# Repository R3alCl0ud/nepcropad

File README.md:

# nepcropad
Me macro pad kb files

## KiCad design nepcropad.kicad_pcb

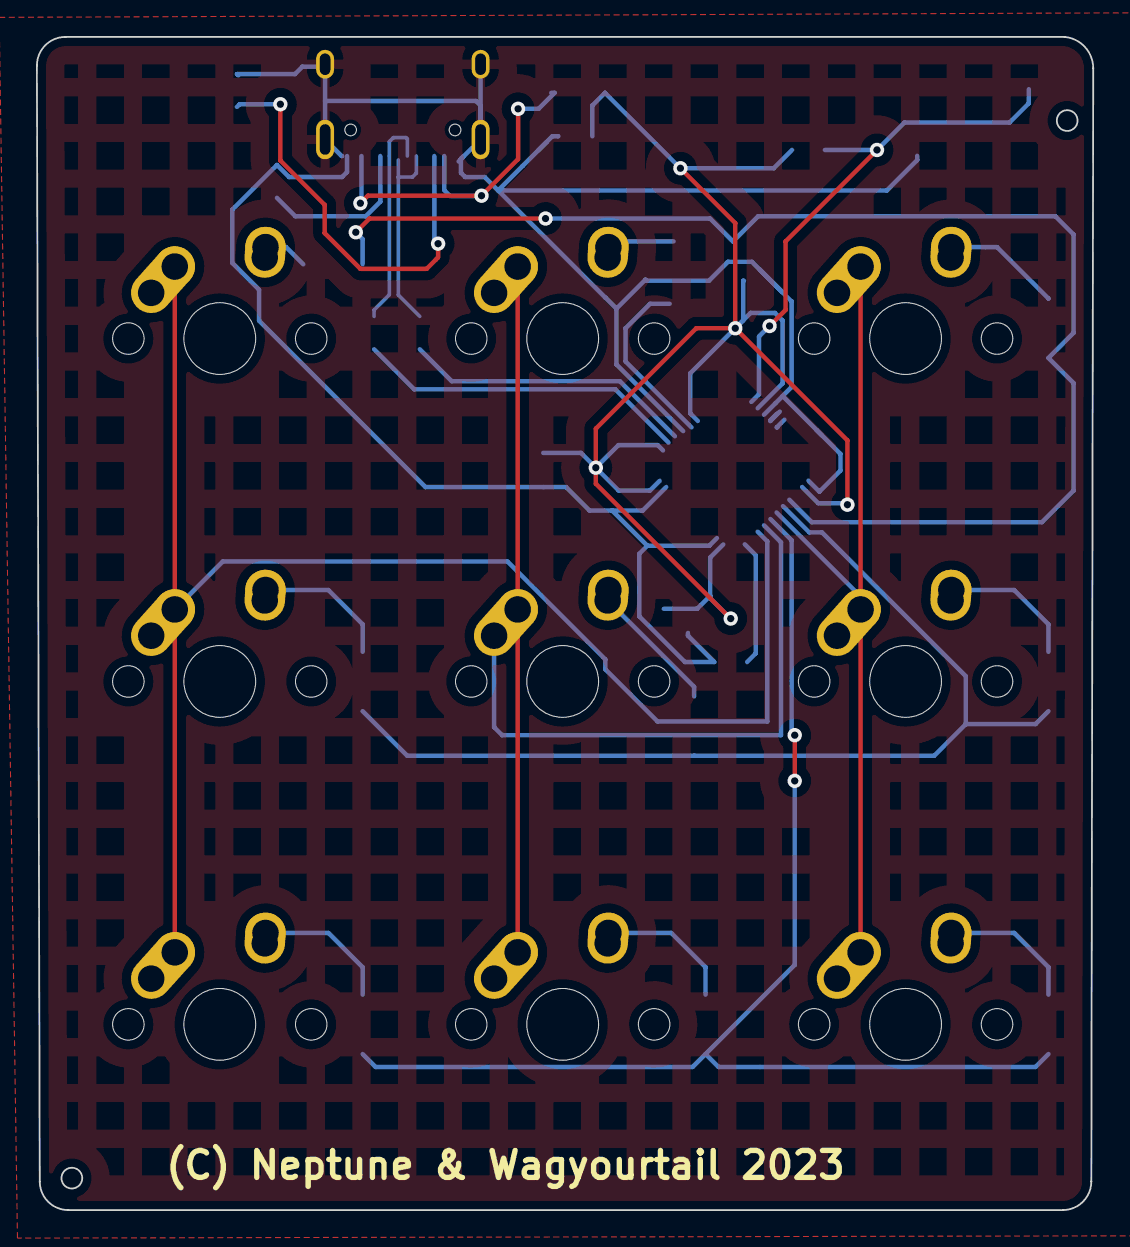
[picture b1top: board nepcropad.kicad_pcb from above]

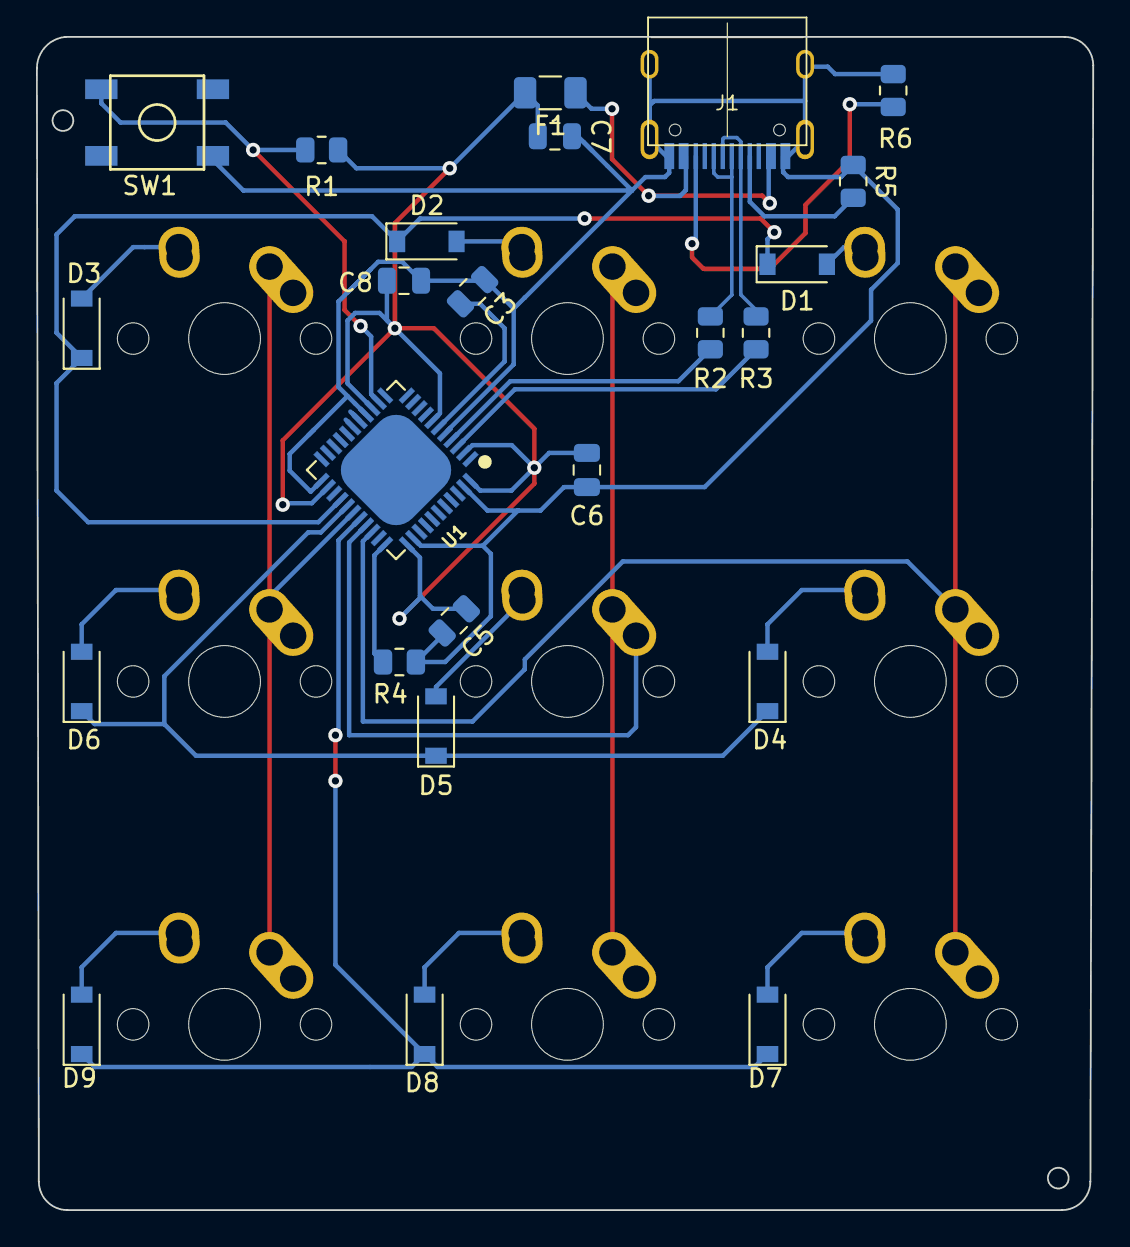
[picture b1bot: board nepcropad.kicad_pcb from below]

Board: 2 copper layers, 58.7 x 65.2 mm, 33 parts (24 on the bottom side), 27 nets.

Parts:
C3: 1uF; C_0805_2012Metric
C5, C6, C8: 0.1uF; C_0805_2012Metric
C7: 10uF; C_0805_2012Metric
D1, D2, D3, D4, D5, D6, D7, D8, D9: D_Small; D_SOD-123
F1: 500mA; Fuse_1206_3216Metric
J1: USB_C_Receptacle_USB2.0; TYPE-C-31-M-12
MX1, MX2, MX3, MX4, MX5, MX6, MX7, MX8, MX9: MX-NoLED; MX-1U-NoLED
R1, R4: 10k; R_0805_2012Metric
R2, R3: 22; R_0805_2012Metric
R5, R6: 5.1k; R_0805_2012Metric
SW1: SW_Push; SKQG-1155865
U1: ATmega32U4-A; QFN44G-0.5-7X7MM

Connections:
+5V: C5.1, C6.1, C7.1, C8.1, F1.2, R1.1, U1.2 (UVCC), U1.7 (VBUS), U1.14 (VCC), U1.24 (AVCC), U1.34 (VCC), U1.44 (AVCC)
COL0: MX1.1 (COL), MX4.1 (COL), MX7.1 (COL), U1.31 (PC6)
COL1: MX2.1 (COL), MX5.1 (COL), MX8.1 (COL), U1.30 (PB6)
COL2: MX3.1 (COL), MX6.1 (COL), MX9.1 (COL), U1.28 (PB4)
D+: J1.A6 (D+), J1.B6 (D+), R2.1
D-: J1.A7 (D-), J1.B7 (D-), R3.1
GND: C3.2, C5.2, C6.2, C7.2, C8.2, J1.A1 (GND), J1.A12 (GND), J1.B1 (GND), J1.B12 (GND), J1.S1 (SHIELD), R4.1, R5.2, R6.2, SW1.1, U1.5 (UGND), U1.15 (GND), U1.23 (GND), U1.35 (GND), U1.43 (GND)
unnamed: C3.1, U1.6 (UCAP)
unnamed: D1.2 (A), MX1.2 (ROW)
unnamed: D2.2 (A), MX2.2 (ROW)
unnamed: D3.2 (A), MX3.2 (ROW)
unnamed: D4.2 (A), MX4.2 (ROW)
unnamed: D5.2 (A), MX5.2 (ROW)
unnamed: D6.2 (A), MX6.2 (ROW)
unnamed: D7.2 (A), MX7.2 (ROW)
unnamed: D8.2 (A), MX8.2 (ROW)
unnamed: D9.2 (A), MX9.2 (ROW)
unnamed: J1.A5 (CC1), R5.1
unnamed: J1.B5 (CC2), R6.1
unnamed: R1.2, SW1.2, U1.13 (~RESET)
unnamed: R2.2, U1.4 (D+)
unnamed: R3.2, U1.3 (D-)
unnamed: R4.2, U1.33 (~HWB/PE2)
ROW0: D1.1 (K), D2.1 (K), D3.1 (K), U1.26 (PD6)
ROW1: D4.1 (K), D5.1 (K), D6.1 (K), U1.27 (PD7)
ROW2: D7.1 (K), D8.1 (K), D9.1 (K), U1.29 (PB5)
VCC: F1.1, J1.A4 (VBUS), J1.A9 (VBUS), J1.B4 (VBUS), J1.B9 (VBUS)

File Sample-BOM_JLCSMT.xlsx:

Comment | Designator | Footprint | JLCPCB Part #（optional）
10uF | C7 | C_0805_2012Metric | C440198
1uF | C3 | C_0805_2012Metric | C28323
100nF | C8,C5,C4,C6 | C_0805_2012Metric | C1853551
500mA Fuse | F1 | Fuse_1206_3216Metric | C355568
5.1k | R5,R6 | R_0805_2012Metric | C2082981
10k | R1,R4 | R_0805_2012Metric | C328719
22 | R2,R3 | R_0805_2012Metric | C2118297
Reset Switch | SW1 | SKQG-1155865 | C127478
1N4148W | D2,D5,D4,D6,D7,D1,D3,D8,D9 | D_SOD-123 | C81598
670688000 | J1 | USB_C_GCT_USB4085 | C9900013983
ATMega32U4 | U1 | TQFP-44_10x10mm_P0.8mm | C45874

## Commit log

2022-11-30 Initial Stuff
    Just following along with the ai03 guide.
2022-11-30 Added part libraries
    from ai03
2022-11-30 The guide said to
    see commit name
2022-11-30 Added key matrix
    and other stuff to the schematic
2022-11-30 PCB Layout
    did the pcb layout
2022-11-30 Done for the night
2022-11-30 Finished routing of SoC area
    Still need to finish routing of the keyswitch matrix.
    I wired the switches together, but not to the soc
2022-11-30 fixed edge cuts
    Idk what happened but they broke again
2022-11-30 Finished routing
    I think atleast.
2022-11-30 Rerouted matrix
    moved closer to soc for more cost efficiency probably.
2022-12-01 add gerbers
2022-12-01 minimize pcb
2022-12-01 move SMC's to same size to cut costs
2022-12-01 move SMC's to same side to cut costs
2022-12-01 cleanup
2022-12-01 move some caps and the timer
2022-12-02 update cap positions
2023-01-31 Should be ready for placing an order
    Added CPL and BOM
    Changed out the USB-C connector as the original one we used is nolonger in production.
2023-01-31 MCU Footprint wrong for new MCU
    I was about to checkout and noticed on the manufacturer's site that the MCU was a different size than the footprint used.
    ATmega32U4-MUR smaller than AU version
2023-01-31 Just a quick fix
    Added gerbers for new version as well
    Cleaned up some routing for the gnd traces
2023-02-01 More routing cleanup
